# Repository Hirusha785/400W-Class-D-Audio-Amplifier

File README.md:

# ⚡ 400W Class-D Audio Amplifier PCB

A custom-designed **400W Class-D Audio Amplifier PCB** developed using **KiCad**.  
This project is based on the **IRS2092S Class-D audio amplifier controller**, featuring a **±55V dual-rail power supply**, discrete MOSFET output stage, transistor-assisted gate-driving circuitry, feedback and compensation networks, bootstrap circuitry, and an LC output filter for efficient high-power audio amplification.

The project demonstrates the complete PCB design workflow in KiCad, including schematic development, component selection, footprint assignment, PCB layout, high-current routing, silkscreen labeling, 3D visualization, and preparation for fabrication.

---

## 📌 Project Overview

The **400W Class-D Audio Amplifier PCB** is a high-power audio electronics project designed around the **IRS2092S Class-D amplifier controller**.

The circuit receives an analog audio input and processes it through the IRS2092S controller. The controller generates high-frequency switching signals that drive the power MOSFET output stage.

The MOSFET half-bridge produces a high-power PWM waveform representing the original audio signal. This switching waveform is then passed through an **LC low-pass output filter**, which removes the high-frequency switching components and delivers the reconstructed amplified audio signal to the speaker.

The PCB has been designed with particular attention to high-current paths, MOSFET gate-drive routing, power distribution, grounding, output filtering, component placement, and thermal management.

> ⚠️ **Note:** The 400W rating represents the intended design target. Actual continuous RMS output power must be confirmed through physical prototype testing and measurement.

---

## ✨ Key Features

- IRS2092S-based Class-D amplifier design
- Approximately 400W target output capability
- ±55V dual-rail DC power supply
- Discrete power MOSFET half-bridge output stage
- Transistor-assisted MOSFET gate-drive circuitry
- Bootstrap high-side gate-drive circuit
- Analog audio input stage
- Feedback and compensation network
- LC low-pass speaker output filter
- Dedicated audio input connector
- Dedicated ±55V power connector
- Dedicated speaker output connector
- High-current PCB routing
- Mixed SMD and through-hole component design
- External heatsink compatibility for power MOSFETs
- Compact custom PCB layout
- Mechanical mounting holes
- Complete KiCad schematic and PCB design
- 3D PCB visualization
- Fabrication-ready PCB structure

---

## 🧠 System Architecture

```txt
Audio Input
      ↓
Input Coupling / Signal Conditioning
      ↓
IRS2092S Class-D Controller
      ↓
PWM / Gate Control Signals
      ↓
Gate Driver Stage
      ↓
Power MOSFET Half-Bridge
      ↓
LC Low-Pass Output Filter
      ↓
Speaker Output
```

---

## ⚙️ Hardware Description

The amplifier PCB is divided into several functional sections:

1. **Audio Input Section**
2. **IRS2092S Controller Section**
3. **Feedback and Compensation Section**
4. **Gate Driver Section**
5. **MOSFET Power Output Stage**
6. **Bootstrap Circuit**
7. **LC Output Filter Section**
8. **Power Supply and Decoupling Section**
9. **Speaker Output Section**

The incoming analog audio signal is fed into the IRS2092S controller through the input coupling and signal-conditioning circuitry.

The IRS2092S generates the required switching signals for the high-side and low-side MOSFETs.

The gate-driving stage improves MOSFET switching performance by providing suitable gate charge and discharge current.

The MOSFET half-bridge then produces a high-frequency PWM output. The LC low-pass filter removes the switching-frequency components and reconstructs the amplified audio waveform before sending it to the speaker.

---

## 🧩 Main Components

| Component | Description |
|---|---|
| IRS2092S | Main Class-D audio amplifier controller |
| Power MOSFETs | High-current half-bridge switching devices |
| 2N3904 | NPN transistor used in gate-drive/support circuitry |
| 2N3906 | PNP transistor used in gate-drive/support circuitry |
| TIP41A | Power transistor used in supporting circuitry |
| Output Inductor | Main inductor of the LC output filter |
| Filter Capacitor | Works with the output inductor to remove PWM switching components |
| Fast Diodes | Used for bootstrap and protection-related functions |
| Electrolytic Capacitors | Power filtering and local energy storage |
| Ceramic / Film Capacitors | High-frequency filtering, decoupling, and compensation |
| Resistors | Biasing, feedback, compensation, and gate control |
| Audio Input Connector | Provides analog audio input |
| Power Terminal | Provides +55V, GND, and -55V supply connections |
| Speaker Terminal | Provides amplified audio output |
| PCB | Custom-designed printed circuit board developed using KiCad |

---

## 🎛️ IRS2092S Controller Section

The amplifier is designed around the **IRS2092S**, a high-performance Class-D audio amplifier controller.

The controller performs several important functions, including:

- PWM generation
- High-side MOSFET control
- Low-side MOSFET control
- Gate-driver management
- Dead-time control
- Feedback processing
- Error amplification
- Oscillation control
- Shutdown functionality
- Bootstrap operation
- Over-current protection support

The IRS2092S acts as the central control component of the amplifier.

---

## 🎚️ Audio Input Section

The audio input section receives the low-level analog audio signal.

The input circuitry provides:

- DC blocking
- Signal coupling
- Input impedance control
- Signal conditioning
- Noise filtering
- Proper signal biasing

### Audio Input Connection

```txt
IN+  → Audio Signal
GND  → Audio Ground
```

A shielded audio cable is recommended to minimize unwanted noise and interference.

---

## ⚡ Power Supply

The amplifier is designed to operate using a symmetrical dual-rail DC power supply.

```txt
+55V
 GND
-55V
```

### Power Input Connection

```txt
+55V → Positive Supply Rail
GND  → Power Ground
-55V → Negative Supply Rail
```

The power supply must provide sufficient current for the intended output power and speaker impedance.

Important power supply considerations include:

- Sufficient current capacity
- Low output ripple
- Large bulk filtering capacitors
- Proper grounding
- Suitable rail fuses
- Correct polarity
- Soft-start or inrush limiting for high-power supplies

> ⚠️ Always verify the supply polarity before powering the PCB.

> ⚠️ ±55V DC is potentially dangerous and can cause electric shock, component failure, fire, or serious damage if handled incorrectly.

---

## 🔥 MOSFET Power Stage

The amplifier uses a discrete MOSFET half-bridge power output stage.

The MOSFET stage performs the high-power switching required for Class-D amplification.

Its main functions include:

- High-frequency switching
- PWM power amplification
- High-current output delivery
- Driving the LC output filter
- Transferring amplified power to the loudspeaker

Important MOSFET characteristics include:

- Drain-source voltage rating
- Drain current rating
- Low RDS(on)
- Gate charge
- Switching speed
- Thermal resistance
- Safe Operating Area

Proper MOSFET cooling is essential for reliable high-power operation.

---

## 🚀 Gate Driver Section

The amplifier includes transistor-assisted gate-driving circuitry between the IRS2092S and the MOSFET output stage.

The gate-driver section helps provide:

- Faster MOSFET switching
- Improved gate charge current
- Faster gate discharge
- Reduced switching losses
- Better MOSFET transition control
- Improved efficiency

Gate resistors are used to control the switching speed and reduce excessive ringing.

---

## ⚙️ Bootstrap Circuit

The high-side MOSFET requires a gate-drive voltage above the switching-node voltage.

A bootstrap circuit is therefore used to provide the required high-side gate-driving voltage.

The bootstrap section typically includes:

- Bootstrap diode
- Bootstrap capacitor
- Associated supply components

### Basic Operation

```txt
Low-Side MOSFET Turns ON
        ↓
Bootstrap Capacitor Charges
        ↓
High-Side Driver Activates
        ↓
High-Side Gate Voltage is Generated
        ↓
High-Side MOSFET Turns ON
```

Correct bootstrap component selection is important for reliable amplifier operation.

---

## 🔄 Feedback and Compensation Section

The amplifier includes a feedback and compensation network connected to the IRS2092S controller.

This section helps provide:

- Stable closed-loop gain
- Improved linearity
- Reduced distortion
- Stable frequency response
- Better output accuracy
- Improved control-loop stability

The feedback routing should be kept away from noisy high-current and high-frequency switching areas wherever possible.

---

## 🌀 LC Output Filter

Class-D amplifiers generate a high-frequency PWM waveform at the MOSFET output stage.

An **LC low-pass filter** is used to remove the switching-frequency components and recover the amplified audio waveform.

### Signal Path

```txt
MOSFET Half-Bridge
        ↓
Switching Node
        ↓
Output Inductor
        ↓
Filter Capacitor
        ↓
Speaker Output
```

The LC output filter helps:

- Remove PWM switching components
- Reduce high-frequency noise
- Reduce EMI
- Recover the audio-frequency waveform
- Prevent excessive switching energy from reaching the speaker

The output inductor must be capable of carrying high current without magnetic saturation.

---

## 🔊 Speaker Output

The amplified and filtered audio signal is provided through the speaker output terminal.

```txt
SPK+ → Amplified Audio Signal
GND  → Speaker Return
```

Typical speaker loads may include:

```txt
4Ω Speaker
8Ω Speaker
```

The safe speaker impedance depends on the MOSFET ratings, power supply capability, thermal performance, and overall circuit design.

---

## 🔢 Output Power Calculation

The approximate amplifier output power can be calculated using:

```txt
P = Vrms² / R
```

Where:

```txt
P     = Output Power in Watts
Vrms  = RMS Output Voltage
R     = Speaker Load Resistance
```

Example:

```txt
Vrms = 40V
R = 4Ω

P = 40² / 4

P = 1600 / 4

P = 400W
```

Therefore:

```txt
40 Vrms into 4Ω ≈ 400W
```

Actual output capability depends on:

- Supply voltage under load
- Speaker impedance
- MOSFET conduction losses
- MOSFET switching losses
- Output filter losses
- PCB resistance
- Power supply current capability
- Cooling
- Distortion limit
- Thermal conditions

---

## 🌡️ Thermal Management

The power MOSFETs require adequate thermal management.

A suitable external heatsink should be installed.

### Typical Thermal Arrangement

```txt
Power MOSFET
      ↓
Thermal Compound
      ↓
Thermal Pad / Electrical Insulator
      ↓
Aluminium Heatsink
      ↓
Natural or Forced Airflow
```

Recommended cooling methods include:

- Large aluminium heatsink
- High-quality thermal compound
- Electrically insulating thermal pads where required
- Proper MOSFET mounting
- Good enclosure ventilation
- Forced-air cooling for prolonged high-power operation

A cooling fan is recommended when operating the amplifier continuously at high output levels.

---

## 🖥️ PCB Design

The PCB was designed using **KiCad** and includes:

- Schematic capture
- Component selection
- Footprint assignment
- PCB layout
- Component placement
- Manual routing
- High-current trace routing
- Power distribution
- Ground routing
- Signal routing
- Silkscreen labeling
- Mounting holes
- 3D PCB visualization
- Fabrication preparation

The board was organized to keep sensitive audio/control circuitry separated from the high-current switching section as much as practical.

---

## ⚡ High-Current PCB Routing

Important high-current paths include:

```txt
Power Supply
     ↓
Power MOSFET Stage
     ↓
Output Inductor
     ↓
Speaker Output
     ↓
Power Ground Return
```

High-current tracks should be:

- Short
- Wide
- Direct
- Low resistance
- Free from unnecessary vias

For higher current capability, thicker PCB copper such as **2 oz copper** can be considered.

---

## ⚡ Switching Node Considerations

The switching node between the MOSFET half-bridge and output inductor is one of the most critical sections of the PCB.

The switching-node copper area should be kept as small as practical.

A large switching node can increase:

- EMI
- Parasitic capacitance
- Ringing
- Noise coupling
- Switching losses

Recommended layout:

```txt
MOSFET Half-Bridge
        ↓
Short Switching Node
        ↓
Output Inductor
```

---

## 🔁 Gate Routing Considerations

The MOSFET gate-drive traces should be:

- Short
- Direct
- Low inductance
- Located away from noisy switching nodes

Recommended routing structure:

```txt
Gate Driver
     ↓
Gate Resistor
     ↓
MOSFET Gate
     ↓
Short Return Path
```

Poor gate routing may result in:

- Ringing
- False MOSFET turn-on
- Shoot-through
- EMI
- Excessive heating
- MOSFET failure

---

## 🌍 Grounding

Grounding is extremely important in Class-D amplifier PCB design.

The design should carefully manage:

```txt
Signal Ground
    ├── Audio Input
    ├── Feedback Circuit
    └── Controller Reference

Power Ground
    ├── MOSFET Current Return
    ├── Speaker Return
    └── Power Supply Return
```

High-current return paths should not flow through sensitive low-level audio ground paths.

---

## 🔋 Decoupling and Filtering

The circuit includes decoupling and filtering components to maintain stable power rails and reduce switching noise.

These include:

- Electrolytic bulk capacitors
- Ceramic bypass capacitors
- Film capacitors
- Bootstrap capacitor
- Local supply decoupling

High-frequency bypass capacitors should be placed close to the relevant switching and control devices.

---

## 🛡️ Recommended Protection Features

Future revisions of the amplifier can include additional protection features such as:

- Speaker DC protection relay
- Power-on speaker delay
- Over-temperature protection
- Over-current protection
- Short-circuit protection
- Supply rail fuses
- Undervoltage protection
- Overvoltage protection
- Soft-start circuitry
- Inrush-current limiting
- Clip indicator
- Fault indicator
- Automatic cooling fan control

---

## 🔊 Speaker Protection

A separate speaker protection circuit is recommended for practical high-power amplifier use.

### Suggested Architecture

```txt
Amplifier Output
      ↓
DC Fault Detection
      ↓
Power-On Delay
      ↓
Protection Relay
      ↓
Speaker
```

This can protect the speaker from:

- DC output faults
- Turn-on transients
- Turn-off transients
- Amplifier failure

---

## 📷 PCB Preview

The project includes schematic, PCB layout, and 3D visualization previews.

### Schematic

### PCB Layout

### 3D View

---

## 🧪 Recommended Testing

Before connecting a loudspeaker, the amplifier should be tested carefully.

Recommended testing sequence:

1. Perform a complete visual inspection.
2. Check for short circuits between the power rails.
3. Verify component orientation and polarity.
4. Apply power using a current-limited supply where possible.
5. Confirm all internal supply voltages.
6. Verify the IRS2092S operation.
7. Check high-side and low-side gate signals using an oscilloscope.
8. Verify correct dead time between MOSFET switching signals.
9. Inspect the switching node waveform.
10. Connect a suitable high-power dummy load.
11. Apply a low-level 1 kHz sine-wave input.
12. Gradually increase the signal level.
13. Monitor output voltage and waveform.
14. Measure MOSFET and output inductor temperatures.
15. Check for clipping and instability.
16. Connect a real speaker only after successful dummy-load testing.

> ⚠️ Appropriate differential or isolated probing techniques must be used when measuring high-side switching waveforms.

---

## 📊 Recommended Performance Measurements

| Measurement | Purpose |
|---|---|
| RMS Output Voltage | Calculate real output power |
| THD+N | Measure audio distortion |
| Frequency Response | Verify audio bandwidth |
| Signal-to-Noise Ratio | Evaluate noise performance |
| DC Offset | Verify speaker safety |
| Efficiency | Evaluate Class-D performance |
| MOSFET Temperature | Verify thermal design |
| Inductor Temperature | Verify output filter performance |
| Switching Frequency | Verify controller operation |
| EMI / EMC | Evaluate switching interference |

---

## 📈 Efficiency

Class-D amplifiers are designed to achieve high efficiency compared with conventional linear amplifier topologies.

Efficiency can be calculated using:

```txt
Efficiency (%) = (Output Power / Input Power) × 100
```

The actual efficiency depends on:

- MOSFET conduction losses
- MOSFET switching losses
- Gate-driver losses
- Output inductor losses
- PCB resistance
- Power supply losses
- Load impedance

---

## 🚀 Applications

This PCB can be used for:

- High-power audio amplifier development
- Class-D amplifier experimentation
- Power electronics learning
- Audio electronics research
- MOSFET switching studies
- Gate-driver circuit experimentation
- High-current PCB design practice
- KiCad PCB design portfolio development
- Audio hardware prototyping
- Educational electronics projects
- Custom speaker amplifier systems

---

## 🔮 Future Improvements

Possible future improvements include:

- Speaker protection relay
- DC fault detection
- Temperature sensing
- Automatic cooling fan controller
- Improved MOSFET gate-loop routing
- Reduced switching-node area
- Improved feedback routing
- Additional EMI filtering
- Optimized snubber network
- Clip indicator
- Fault indicator LEDs
- Soft-start circuitry
- Inrush-current limiting
- Balanced audio input
- Differential audio input
- Higher-current connectors
- Improved heatsink mounting
- Additional PCB test points

---

## ⚠️ Safety Notice

This project operates using relatively high DC voltage and potentially very high current.

Potential hazards include:

- Electric shock
- Severe burns
- Fire
- Exploding capacitors
- MOSFET failure
- Loudspeaker damage
- Power supply damage
- Test equipment damage

Large electrolytic capacitors may remain charged after power is removed.

Always:

- Disconnect the power before touching the PCB
- Verify that capacitors are fully discharged
- Use appropriate fuses
- Use current limiting during first power-up
- Use insulated tools
- Verify power polarity
- Use correct oscilloscope probing techniques
- Do not connect expensive speakers during initial testing

This project should only be assembled and tested by individuals familiar with high-power electronics, Class-D amplifiers, PCB troubleshooting, and electrical laboratory safety.

---

## 👨‍💻 Author

**Fernando S.M.H.G.**

Designed using **KiCad**.

Project work includes:

- Schematic design
- Component selection
- Footprint assignment
- PCB placement
- High-current routing
- Signal routing
- Power routing
- Grounding design
- Silkscreen design
- 3D PCB visualization
- Mechanical PCB layout

---

## 📜 License

This project is licensed under the **MIT License**.

You are free to use, copy, modify, merge, publish, distribute, sublicense, and/or sell copies of the project files, subject to the terms of the MIT License.

See the `LICENSE` file for complete details.

### MIT License

```txt
MIT License

Copyright (c) 2026 Fernando S.M.H.G.

Permission is hereby granted, free of charge, to any person obtaining a copy
of this project and associated documentation files (the "Project"), to deal
in the Project without restriction, including without limitation the rights
to use, copy, modify, merge, publish, distribute, sublicense, and/or sell
copies of the Project, and to permit persons to whom the Project is
furnished to do so, subject to the following conditions:

The above copyright notice and this permission notice shall be included in
all copies or substantial portions of the Project.

THE PROJECT IS PROVIDED "AS IS", WITHOUT WARRANTY OF ANY KIND, EXPRESS OR
IMPLIED, INCLUDING BUT NOT LIMITED TO THE WARRANTIES OF MERCHANTABILITY,
FITNESS FOR A PARTICULAR PURPOSE AND NONINFRINGEMENT. IN NO EVENT SHALL THE
AUTHORS OR COPYRIGHT HOLDERS BE LIABLE FOR ANY CLAIM, DAMAGES OR OTHER
LIABILITY, WHETHER IN AN ACTION OF CONTRACT, TORT OR OTHERWISE, ARISING FROM,
OUT OF OR IN CONNECTION WITH THE PROJECT OR THE USE OR OTHER DEALINGS IN
THE PROJECT.
```

---

## ⚠️ Disclaimer

This project is provided **"AS IS"** without warranty.

The author does not guarantee:

- 400W continuous RMS output
- Electrical safety
- Commercial suitability
- Regulatory compliance
- EMI / EMC compliance
- Specific audio performance
- Thermal performance
- Long-term reliability

Anyone building or modifying this design is responsible for verifying:

- Circuit correctness
- Component ratings
- MOSFET ratings
- PCB current capability
- Trace widths
- Electrical clearances
- Thermal performance
- Protection circuitry
- Power supply capability
- Electrical safety

The author is not responsible for personal injury, equipment damage, loudspeaker damage, fire, incorrect assembly, semiconductor failure, or other losses resulting from the construction or use of this project.

---

## ⭐ Support

If you find this project useful:

- ⭐ Star the repository
- 🍴 Fork the project
- 🔧 Suggest improvements
- 🐛 Report design issues
- 📢 Share the project with electronics enthusiasts

---

<p align="center">
  <b>⚡ 400W Class-D Audio Amplifier PCB ⚡</b>
</p>

<p align="center">
  IRS2092S-Based High-Power Audio Amplifier & Custom PCB Design
</p>

<p align="center">
  Designed with ❤️ using KiCad
</p>

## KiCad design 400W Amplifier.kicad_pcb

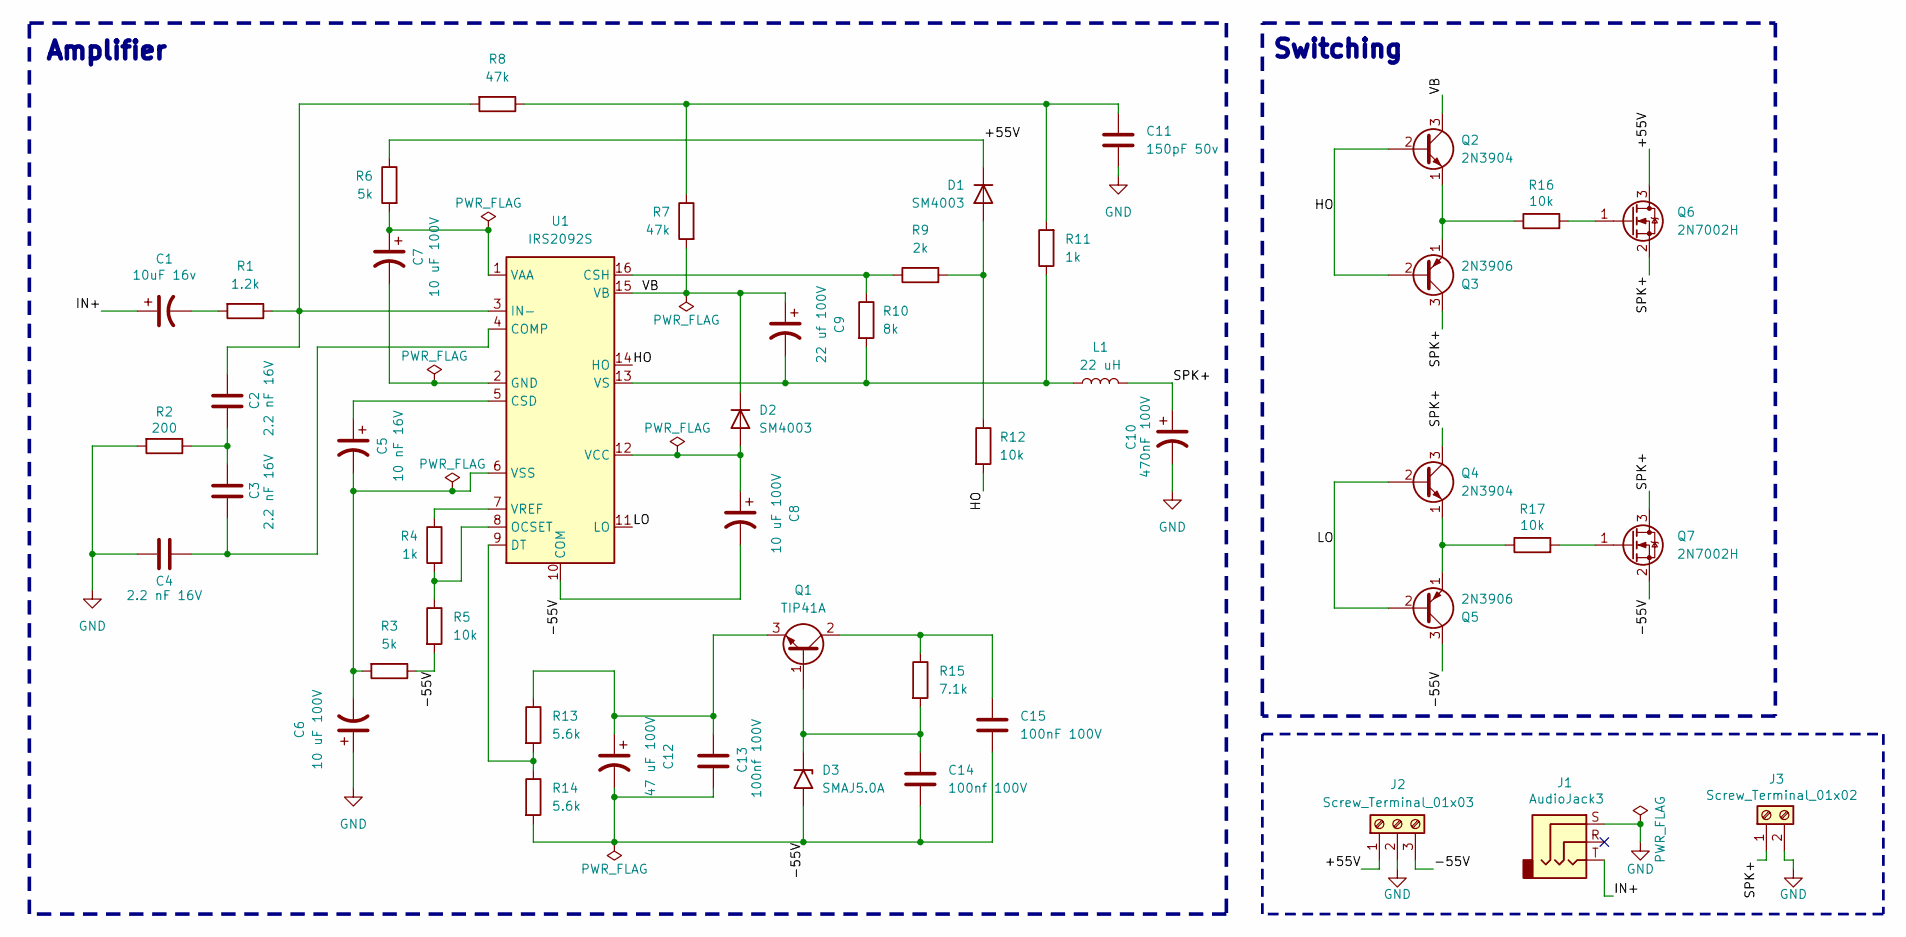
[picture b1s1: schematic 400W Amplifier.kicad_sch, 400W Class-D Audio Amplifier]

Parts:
C1: 10uF 16v; CP_Radial_D5.0mm_P2.50mm
C2, C3, C4: 2.2 nF 16V; C_0805_2012Metric
C5: 10 nF 16V; C_0805_2012Metric
C6: 10 uF 100V; C_Radial_D6.3mm_H5.0mm_P2.50mm
C7: 10 uF 100V; C_1210_3225Metric
C8: 10 uF 100V; CP_Radial_D6.3mm_P2.50mm
C9: 22 uf 100V; CP_Radial_D8.0mm_P2.50mm
C10: 470nF 100V; C_1206_3216Metric
C11: 150pF 50v; C_0805_2012Metric
C12: 47 uF 100V; C_1206_3216Metric
C13: 100nf 100V; C_Radial_D16.0mm_H25.0mm_P7.50mm
C14: 100nf 100V; C_1206_3216Metric
C15: 100nF 100V; C_1206_3216Metric
D1, D2: SM4003; D_MELF
D3: SMAJ5.0A; D_SMA
J1: AudioJack3; CUI_SJ-3523-SMT-TR
J2: Screw_Terminal_01x03; TerminalBlock_Phoenix_MKDS-1,5-3_1x03_P5.00mm_Horizontal
J3: Screw_Terminal_01x02; TerminalBlock_Phoenix_MKDS-1,5-2_1x02_P5.00mm_Horizontal
L1: 22 uH; L_Toroid_Vertical_L24.6mm_W15.5mm_P11.44mm_Pulse_KM-4
Q1: TIP41A; TO-220-3_Vertical
Q2, Q4: 2N3904; TO-92_Inline
Q3, Q5: 2N3906; TO-92_Inline
Q6, Q7: 2N7002H; SOT-23
R1: 1.2k; R_0805_2012Metric
R2: 200; R_0805_2012Metric
R3, R6: 5k; R_0805_2012Metric
R4, R11: 1k; R_0805_2012Metric
R5, R12, R16, R17: 10k; R_0805_2012Metric
R7, R8: 47k; R_0805_2012Metric
R9: 2k; R_0805_2012Metric
R10: 8k; R_0805_2012Metric
R13, R14: 5.6k; R_0805_2012Metric
R15: 7.1k; R_0805_2012Metric
U1: IRS2092S; SOIC-16_3.9x9.9mm_P1.27mm

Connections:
/+55V: D1.1 (K), J2.1, Q6.3 (D), R6.1
/-55V: C8.2, C12.2, C13.2, C14.2, C15.2, D3.2 (A2), J2.3, Q5.3 (C), Q7.2 (S), R3.1, R5.2, R14.2, U1.10 (COM)
/HO: Q2.2 (B), Q3.2 (B), R12.2, U1.14 (HO)
/IN+: C1.1, J1.T
/LO: Q4.2 (B), Q5.2 (B), U1.11 (LO)
/SPK+: C10.1, J3.1, L1.2, Q3.3 (C), Q4.3 (C), Q6.2 (S), Q7.3 (D)
/VB: C9.1, D2.1 (K), Q2.3 (C), R7.2, U1.15 (VB)
GND: C4.2, C6.1, C10.2, C11.2, J1.S, J2.2, J3.2, R2.2
unnamed: C1.2, R1.2
unnamed: C2.2, C3.1, R2.1
unnamed: C11.1, R7.1, R8.1, R11.2
unnamed: D1.2 (A), R9.2, R12.1
unnamed: C8.1, D2.2 (A), U1.12 (VCC)
unnamed: C14.1, D3.1 (A1), Q1.1 (B), R15.2
unnamed: C15.1, Q1.2 (C), R15.1
unnamed: C12.1, C13.1, Q1.3 (E), R13.1
unnamed: Q2.1 (E), Q3.1 (E), R16.1
unnamed: Q4.1 (E), Q5.1 (E), R17.1
unnamed: Q6.1 (G), R16.2
unnamed: Q7.1 (G), R17.2
unnamed: C3.2, C4.1, U1.4 (COMP)
unnamed: C5.1, U1.5 (CSD)
unnamed: R9.1, R10.1, U1.16 (CSH)
unnamed: R13.2, R14.1, U1.9 (DT)
unnamed: C7.2, U1.2 (GND)
unnamed: C2.1, R1.1, R8.2, U1.3 (IN-)
unnamed: R4.2, R5.1, U1.8 (OCSET)
unnamed: C7.1, R6.2, U1.1 (VAA)
unnamed: R4.1, U1.7 (VREF)
unnamed: C9.2, L1.1, R10.2, R11.1, U1.13 (VS)
unnamed: C5.2, C6.2, R3.2, U1.6 (VSS)

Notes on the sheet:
Switching
Amplifier

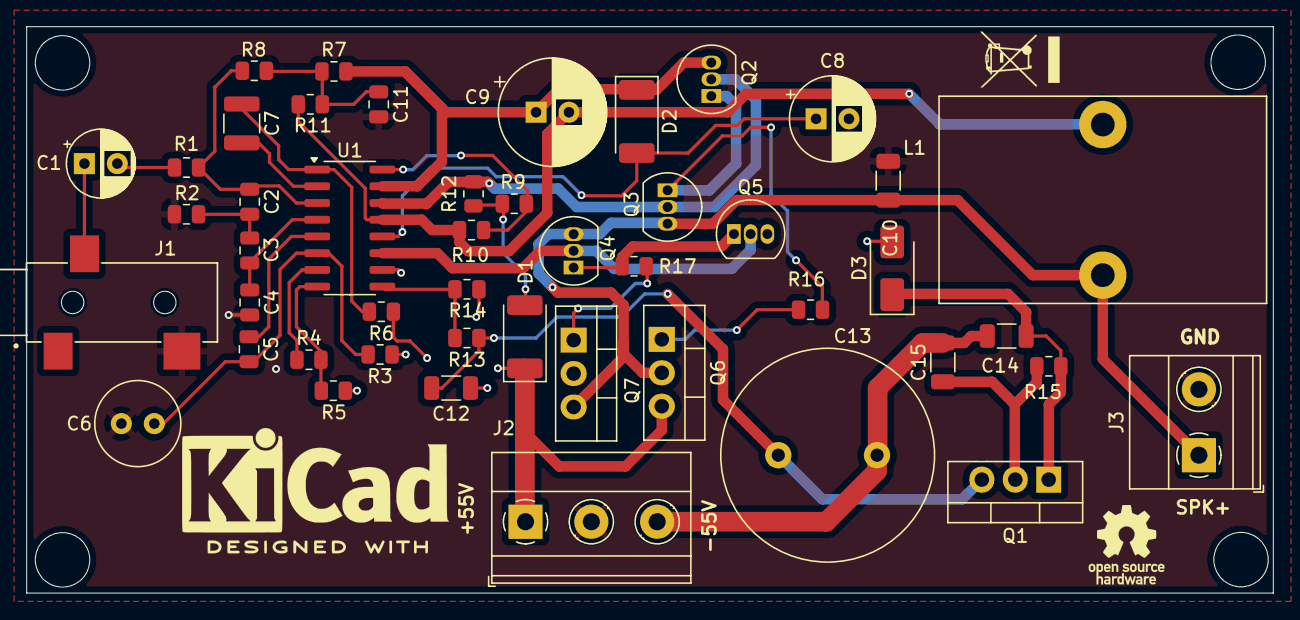
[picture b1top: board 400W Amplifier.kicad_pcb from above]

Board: 4 copper layers, 94.7 x 43.0 mm, 47 parts (0 on the bottom side), 31 nets.

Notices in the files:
README.md:
License: MIT
